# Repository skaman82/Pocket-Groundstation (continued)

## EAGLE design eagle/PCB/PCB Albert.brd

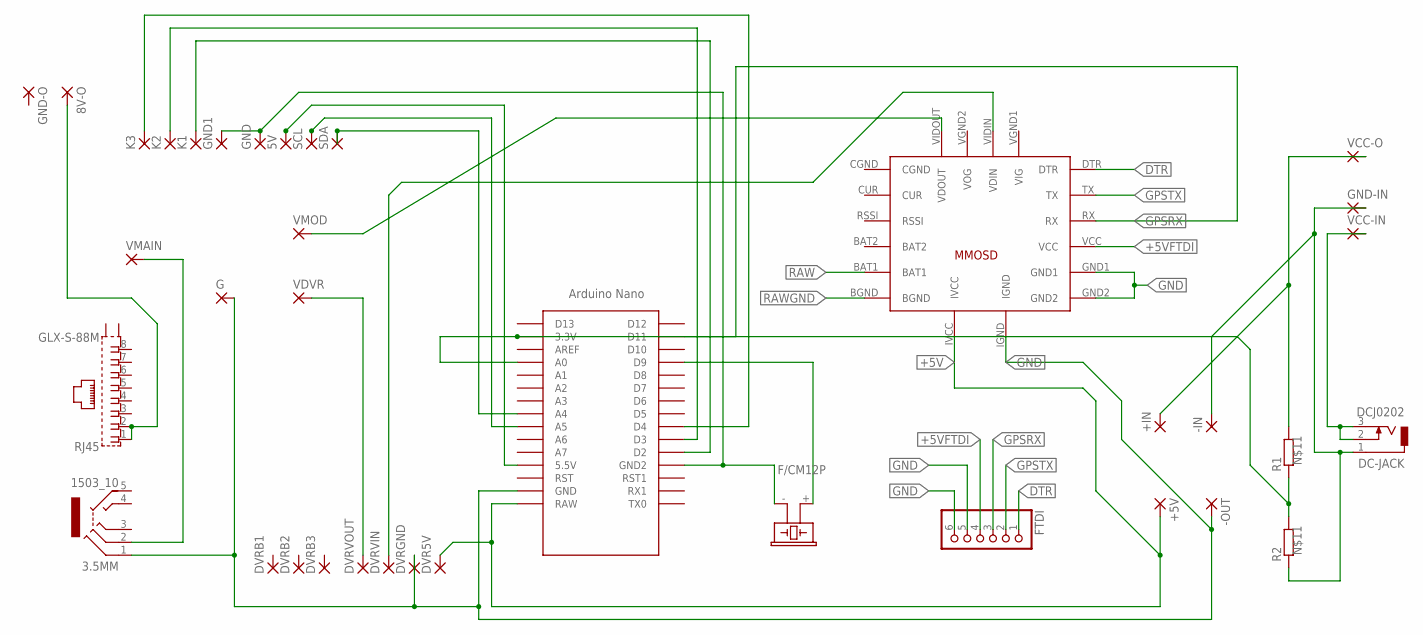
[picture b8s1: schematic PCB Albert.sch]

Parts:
3.5MM: 1503_10
5V: SMD2; SMD1,27-2,54
8V-O: 2,54/1,1
+5V: SMD2; SMD1,27-2,54
+IN: SMD2; SMD1,27-2,54
-IN: SMD2; SMD1,27-2,54
-OUT: SMD2; SMD1,27-2,54
ADRUINO-NANO: NANO
BUZZ: F/CM12P
DC-JACK: DCJ0202
DVR5V: SMD2; SMD1,27-2,54
DVRB1, DVRB2, DVRB3: SMD2; SMD1,27-2,54
DVRGND: SMD2; SMD1,27-2,54
DVRVIN: SMD2; SMD1,27-2,54
DVRVOUT: SMD2; SMD1,27-2,54
FTDI: PINHD-1X6; 1X06
G: SMD2; SMD1,27-2,54
GND, GND1: SMD2; SMD1,27-2,54
GND-IN: 2,54/1,1
GND-O: 2,54/1,1
K1, K2, K3: SMD2; SMD1,27-2,54
MINIMOSD: MICROMINIMOSDPWR; MMOSDNVDVID
R1, R2: R0207/10; 0207/10
RJ45: GLX-S-88M
SCL: SMD2; SMD1,27-2,54
SDA: SMD2; SMD1,27-2,54
VCC-IN: 2,54/1,1
VCC-O: 2,54/1,1
VDVR: SMD2; SMD1,27-2,54
VMAIN: SMD2; SMD1,27-2,54
VMOD: SMD2; SMD1,27-2,54

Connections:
+5V: +5V.1, ADRUINO-NANO.RAW, DVR5V.1, MINIMOSD.IVCC
+5VFTDI: FTDI.4, MINIMOSD.VCC
BAT2: MINIMOSD.BAT2
CGND: MINIMOSD.CGND
DTR: FTDI.1, MINIMOSD.DTR
GND: 3.5MM.1, -OUT.1, ADRUINO-NANO.GND, DVRGND.1, FTDI.5, FTDI.6, G.1, MINIMOSD.GND1, MINIMOSD.GND2, MINIMOSD.IGND
GPSRX: ADRUINO-NANO.D11, FTDI.3, MINIMOSD.RX
GPSTX: FTDI.2, MINIMOSD.TX
unnamed: ADRUINO-NANO.GND1 (GND2), BUZZ.- (2), GND.1, GND1.1
unnamed: 5V.1, ADRUINO-NANO.5V (5.5V)
unnamed: ADRUINO-NANO.A5, SCL.1
unnamed: ADRUINO-NANO.A4, SDA.1
unnamed: DC-JACK.2, DC-JACK.3, VCC-IN.1
unnamed: 8V-O.1, RJ45.1, RJ45.2
unnamed: ADRUINO-NANO.D2, K1.1
unnamed: ADRUINO-NANO.D3, K2.1
unnamed: ADRUINO-NANO.D4, K3.1
unnamed: ADRUINO-NANO.D9, BUZZ.+ (1)
unnamed: -IN.1, DC-JACK.1, GND-IN.1, R2.1
unnamed: DVRVOUT.1, VDVR.1
unnamed: 3.5MM.2, VMAIN.1
unnamed: +IN.1, R1.2, VCC-O.1
unnamed: ADRUINO-NANO.3.3V, ADRUINO-NANO.A0, R1.1, R2.2
RAW: MINIMOSD.BAT1
RAWGND: MINIMOSD.BGND
VIDIN: DVRVIN.1, MINIMOSD.VIDIN (VDIN)
VIDOUT: MINIMOSD.VIDOUT (VDOUT), VMOD.1

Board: 2 copper layers, 37 parts (0 on the bottom side), 23 nets, no tracks yet.

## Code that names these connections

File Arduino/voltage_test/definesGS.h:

#define Voltagedetect          3.4  // Min. voltage for Detection
#define max_cellvoltage        4.2  //Max. cell voltage

#define note                   262  // C4

#define R1                   18000  // Resistor 1
#define R2                    4680  // Resistor 2 (measured)
#define alarmADDR                1  // EEPROM Adress
#define layoutADDR               2  // OSD Layout Adress
#define dvrADDR                  3  // DVR Settings Adress
#define rssiADDR                 4  // DVR Settings Adress

#define BUTTON1_PIN              3  // Button 1
#define BUTTON2_PIN              4  // Button 2
#define BUTTON3_PIN              2  // Button 3
#define DVR1_PIN                 5  // DVR Button 1
#define DVR2_PIN                 6  // DVR Button 2
#define DVR3_PIN                 7  // DVR Button 3
#define DVR_SENS                A1  // DVR LED Sensor
#define STATUS_LED              13  // Status LED
#define beeppin                  8  // Beeper Pin (changed from 9)

#define DELAY                    2  // Delay per loop in ms
#define longpresstime         1000  // in ms

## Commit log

2018-05-25 Some initial concept files
2018-05-25 More 3D work
2018-05-25 new stl
2018-05-26 Update README.md
    Initial parts list
2018-05-26 some test code
2018-05-26 third button added
2018-05-26 delete
2018-05-28 small change
2018-05-28 Voltage Divider + cleanup
    Added Voltage Divider.
    Little Cleanup and beeping works now with tone.
2018-05-28 Added Voltage Detection
    Added Voltage Detection and minor stuff
2018-05-28 Handle Buttons
2018-05-28 add icons
2018-05-28 icons cleanup
2018-05-28 screen layout change
2018-05-29 voltage detection cleanup
2018-05-29 rowork battery alarm
2018-05-29 adjustable alarm
2018-05-29 OLED layout
2018-05-29 3d work
2018-05-29 3D update
2018-05-29 New font file
2018-05-30 new logo
2018-05-30 Logo change
2018-05-31 Initail OSD code
2018-05-31 update font files
2018-06-02 adding docs
2018-06-02 pinCS change
2018-06-02 improve osd code
2018-06-04 EEPROM + OSD Communication
    EEPROM + OSD Communication + Code Layout Cleanup + Small Changes
2018-06-04 Receive
    Receive
2018-06-04 Other Bitshift stuff
    Other Bitshift stuff
2018-06-05 some tests
2018-06-05 adjusting "v" printout if voltage is >10v
2018-06-05 Splash screen and initial menu graphics
2018-06-05 Menu
    Menu
2018-06-05 Small Menu Fix
    Small Menu Fix
2018-06-05 Toilettensmileyhiereinfuegen
    Toilettensmileyhiereinfuegen
2018-06-05 OSD On/Off
    OSD On/Off
2018-06-05 osdsend less often
    osdsend less often
2018-06-05 C3
    C3
2018-06-05 Font update
2018-06-05 splash screen change
2018-06-05 Send Fix
    Send Fix
2018-06-05 softserial fix
    softserial fix
2018-06-05 rx
    rx
2018-06-06 Logic
2018-06-06 PCB work
2018-06-06 menu concept work
2018-06-07 osd test parameters
2018-06-07 comment
2018-06-08 More PCB work
2018-06-08 PCB Update
2018-06-11 Update parts
2018-06-11 Update PCB components
2018-06-11 PCB updates
2018-06-12 added further info about serial protocol moved protocol files to separate folder
2018-06-12 add submenu
2018-06-13 small PCB updates
2018-06-13 minor pcb adjustments
2018-06-14 Component change
2018-06-14 resistor values
2018-06-14 ref voltage
2018-06-14 maybe a fix
    maybe a fix
2018-06-14 Variablen
    Variablen
2018-06-14 Bitmap to external file
    Bitmap to external file
2018-06-14 battery_health
    battery_health
2018-06-15 Menus
2018-06-15 small changes
2018-06-15 menu fix
2018-06-15 new bitmaps
2018-06-15 Submenu Icons
2018-06-15 change button direction
2018-06-15 health
2018-06-15 health2
2018-06-15 dynamic battery icon
    changes according the set min cell voltage alarm
2018-06-15 comments
2018-06-15 Experimental DVR control
2018-06-16 delays
2018-06-16 checking dvr status with DVR LED sensing
2018-06-16 dvr sensor
2018-06-16 osd splash screen
2018-06-17 DVR contorl and some osd changes
2018-06-17 menu work
2018-06-18 Fixez and stuff
2018-06-18 temp osd fix
2018-06-18 OSD rssi
2018-06-18 clear screen on layout change
2018-06-18 remove some dvr menu buttons
2018-06-18 dvr control
2018-06-19 remove serial print
2018-06-19 statusLED
2018-06-19 LED change
2018-06-19 DVR shortcut
2018-06-19 PCB change
2018-06-20 dvr fix
2018-06-21 Status LED
2018-06-21 change led
2018-06-21 ledcheck
2018-06-21 DVR indicator on OLED
2018-06-21 more led conditions
2018-06-21 reduce beeper code
2018-06-21 Reducing code size
2018-06-21 dvr record indicator in menus
2018-06-21 final dvr menu layout
2018-06-21 bot more accurate voltage scaling
2018-06-21 PWM videoswitch support
2018-06-22 OSD layouts
2018-06-22 cleaning up
2018-06-22 DVR autostart placeholder
2018-06-23 New PCB versions
    • Changed buzzer pin to D9
    • D8 goes to PCB 2 now
    • PCB 2 has a new option for mounting a PWM videoswitch
2018-06-25 insert changes
2018-06-25 Insert work
2018-06-26 removing delays
2018-06-26 layout buffer
2018-06-26 refreshing adjustments
2018-06-26 small fix
2018-06-26 fixing
2018-06-26 osd warnings
2018-06-29 new protocol for osd communication
2018-06-29 now using received values on osd
2018-06-29 fixed arduino code to send proper values to osd
2018-06-30 case work
2018-06-30 slicer files
2018-07-01 case modification
2018-07-01 case
2018-07-01 case v2
2018-07-04 PCB and Case changes
2018-07-05 Updates
    • 3D work
    • Cleaning up
2018-07-06 Small PCB change
2018-07-09 new defaults
2018-07-12 Case work and tiny PCB changes
2018-07-13 new defults for voltage reading and warning beeper synct with LED
2018-07-18 Adding Case cover and a cable junction box
2018-07-18 Cleanup
2018-07-18 More cleanup
2018-07-18 Case photos
2018-07-18 more cleaning up
2018-07-18 Datasheet
2018-07-19 Update Battery Icon
2018-07-20 MAX Library Udate
2018-08-02 Alternative 3D formats
2018-10-27 Remove old gerber files
2018-10-28 image update
2018-10-28 removed switch from concept drawing
2018-10-31 updated gitignore for visual studio projects
2018-10-31 small simulation environment in visual studio for trueD protocol
2018-10-31 first implementation of the trueD protocol parsing
2018-11-01 TrueD (dockking firmware) support
    • AutoDVR (start/stopp based on RSSI values)
    • Alternative layout for the main screen with RSSI, band & channel data
2018-11-01 enable the low voltage buzzer again
2018-11-01 position change
2018-11-02 Wireplan
2018-11-02 change photo
2018-11-08 voltage detection changes
2018-11-12 RSS Layout changes and Auto-DVR improvements
2018-11-14 Scaled 3D files & added a magnet stand
2018-11-15 Added Audio connection
2018-11-16 STL-file for the coverplate
2018-11-16 added a thicker version
2018-11-23 added svg forma
2018-11-28 bugfix
2018-11-29 Updated PCBs
    • Round edges
    • Covered vias on PCB1
    • OLED pin swap (VCC <> GND) on PCB2
2018-12-27 New PCB revision (added a cap)
2019-01-03 EAGLE libs
2019-01-04 reduced codesize
2019-01-23 Experimental OSD Addon-PCB
2019-02-12 Experimental PCBs
2019-07-08 new pcb1 revision 3 (5v on RJ45 and OSD PCB footprint added)
2019-07-08 added 75ohm resistor to pcb
